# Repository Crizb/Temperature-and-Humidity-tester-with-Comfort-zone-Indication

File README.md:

# Temperature and Humidity tester with Comfort zone Indication

A simple device which goal was to tell its user the actual temperature and humidity of the enviroment. 
Also the display text saying something about temperature and humidity.

Device based on ATMEGA microcontroller, nokia 5110 display and the "power supply" was based on a few voltage regulators and 18650 Li-Ion battery for portability.

This project was just a 1-Day thing which Was created of pure boredom and from curosity how fast can I design, Etch a PCB and program a simple device.
It was never meant to be professional.

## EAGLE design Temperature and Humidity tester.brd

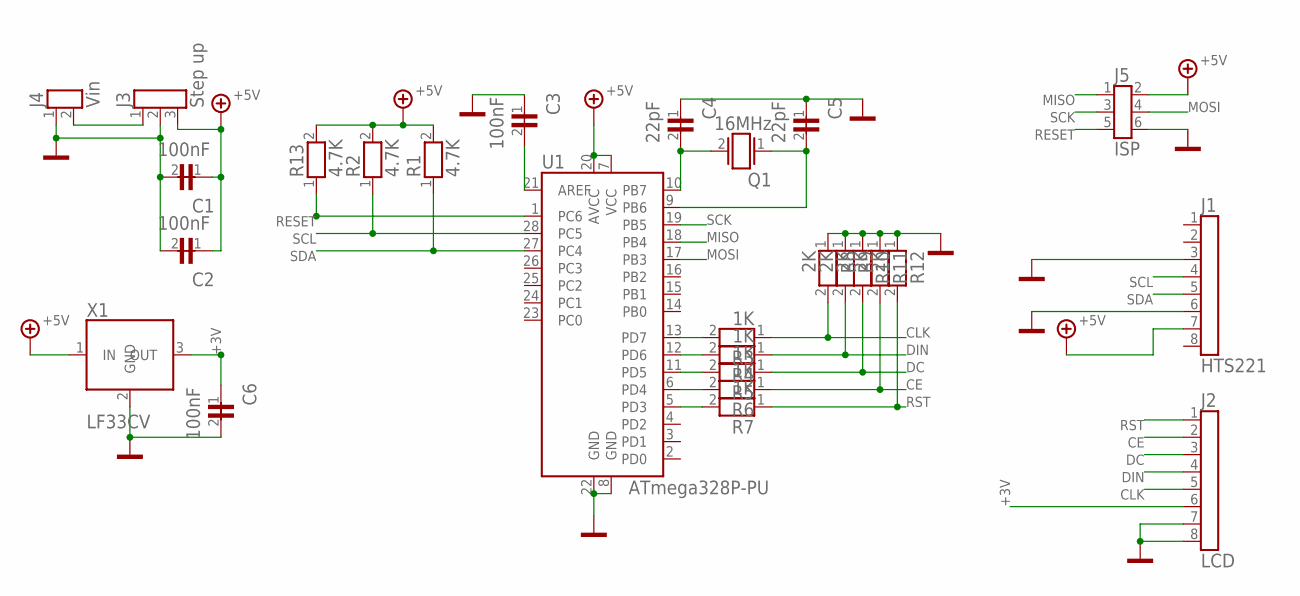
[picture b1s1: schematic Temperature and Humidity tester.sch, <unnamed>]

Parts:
C1: 100nF; 3X5R2,54_42
C2: 100nF; 3X5R2,54_43
C3: 100nF; 3X5R2,54_44
C4: 22pF; 6X6R2,54_DISC_47
C5: 22pF; 6X6R2,54_DISC_48
C6: 100nF; 3X5R2,54_66
J1: HTS221; STIFTLEISTE_1X08_G_2,54_1
J2: LCD; STIFTLEISTE_1X08_G_2,54_2
J3: Step up; STIFTLEISTE_1X03_G_2,54_3
J4: Vin; STIFTLEISTE_1X02_G_2,54_4
J5: ISP; STIFTLEISTE_2X03_G_2,54_59
Q1: 16MHz; HC49/U_46
R1: 4.7K; 0204_MET_27
R2: 4.7K; 0204_MET_28
R3: 1K; 0204_MET_31
R4: 1K; 0204_MET_32
R5: 1K; 0204_MET_33
R6: 1K; 0204_MET_34
R7: 1K; 0204_MET_35
R8: 2K; 0204_MET_36
R9: 2K; 0204_MET_37
R10: 2K; 0204_MET_38
R11: 2K; 0204_MET_39
R12: 2K; 0204_MET_40
R13: 4.7K; 0204_MET_57
U1: ATmega328P-PU; DIL28_WB7,62_P2,54_0
X1: LF33CV; TO220_62

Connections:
2: J3.1, J4.2
+3V: C6.1, J2.6, X1.3 (OUT)
+5V: C1.1, C2.1, J1.7, J3.3, J5.2, R1.2, R2.2, R13.2, U1.7 (VCC), U1.20 (AVCC), X1.1 (IN)
AREF: C3.2, U1.21 (AREF)
CE: J2.2, R6.1, R11.2
CLK: J2.5, R3.1, R8.2
DC: J2.3, R5.1, R10.2
DIN: J2.4, R4.1, R9.2
GND: C1.2, C2.2, C3.1, C4.1, C5.1, C6.2, J1.3, J1.6, J2.7, J2.8, J3.2, J4.1, J5.6, R8.1, R9.1, R10.1, R11.1, R12.1, U1.8 (GND), U1.22 (GND), X1.2 (GND)
MISO: J5.1, U1.18 (PB4)
MOSI: J5.4, U1.17 (PB3)
PB6: C5.2, Q1.1, U1.9 (PB6)
PB7: C4.2, Q1.2, U1.10 (PB7)
PD4: R6.2, U1.6 (PD4)
PD6: R4.2, U1.12 (PD6)
RESET: J5.5, R13.1, U1.1 (PC6)
RST: J2.1, R7.1, R12.2
SCK: J5.3, U1.19 (PB5)
SCL: J1.4, R2.1, U1.28 (PC5)
SDA: J1.5, R1.1, U1.27 (PC4)
SIG$33: R3.2, U1.13 (PD7)
SIG$35: R5.2, U1.11 (PD5)
SIG$37: R7.2, U1.5 (PD3)

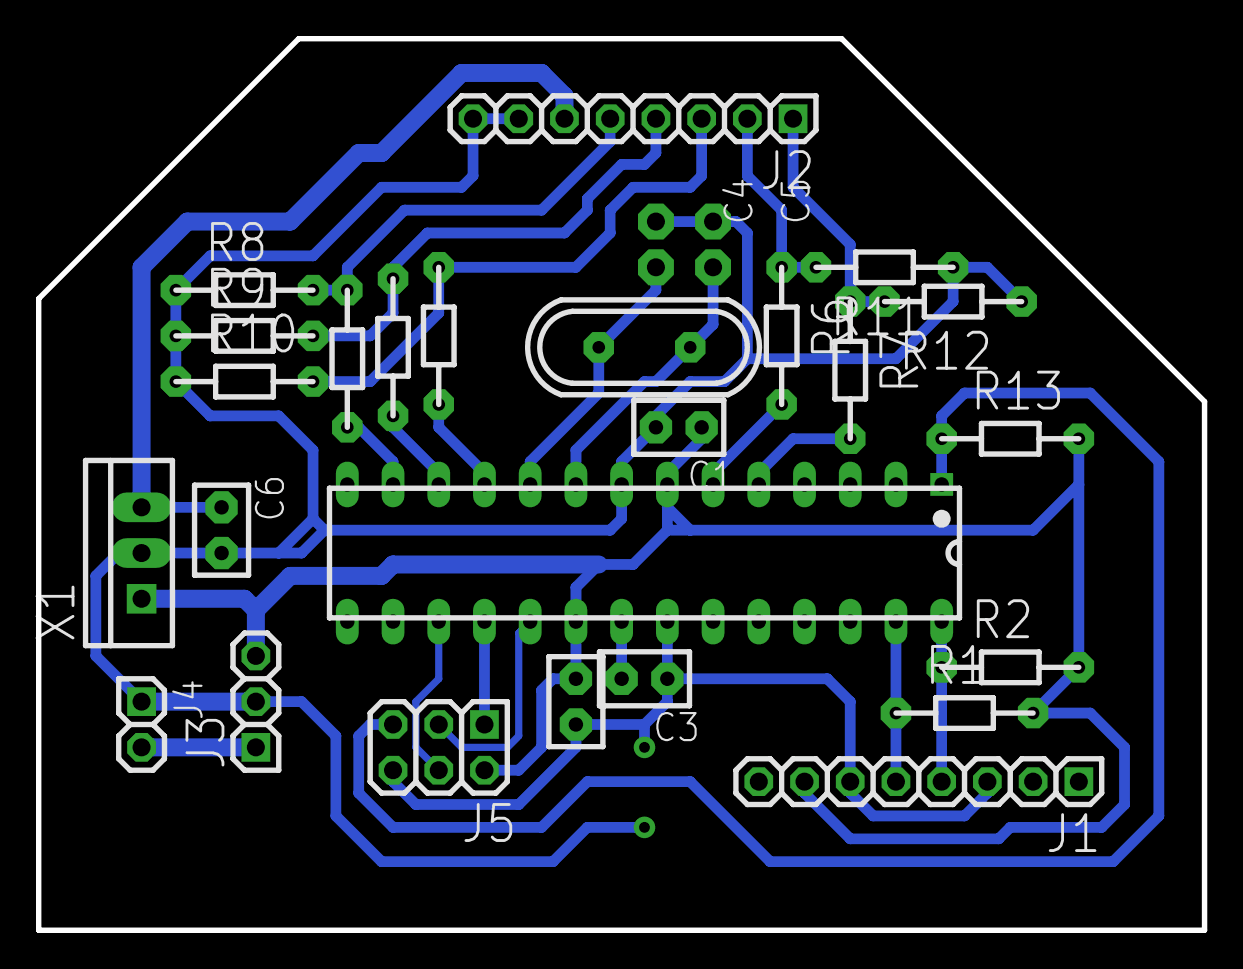
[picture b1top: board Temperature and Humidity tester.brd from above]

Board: 2 copper layers, 64.8 x 49.5 mm, 27 parts (0 on the bottom side), 23 nets.

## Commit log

2020-08-12 Eagle Board File
2020-08-12 Arduino Code
2020-08-12 Schematic to preview
